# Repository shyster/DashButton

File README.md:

# DashButton
Dash Button ESP8266
Kulasov Vladislav
kulasov[@]gmail.com

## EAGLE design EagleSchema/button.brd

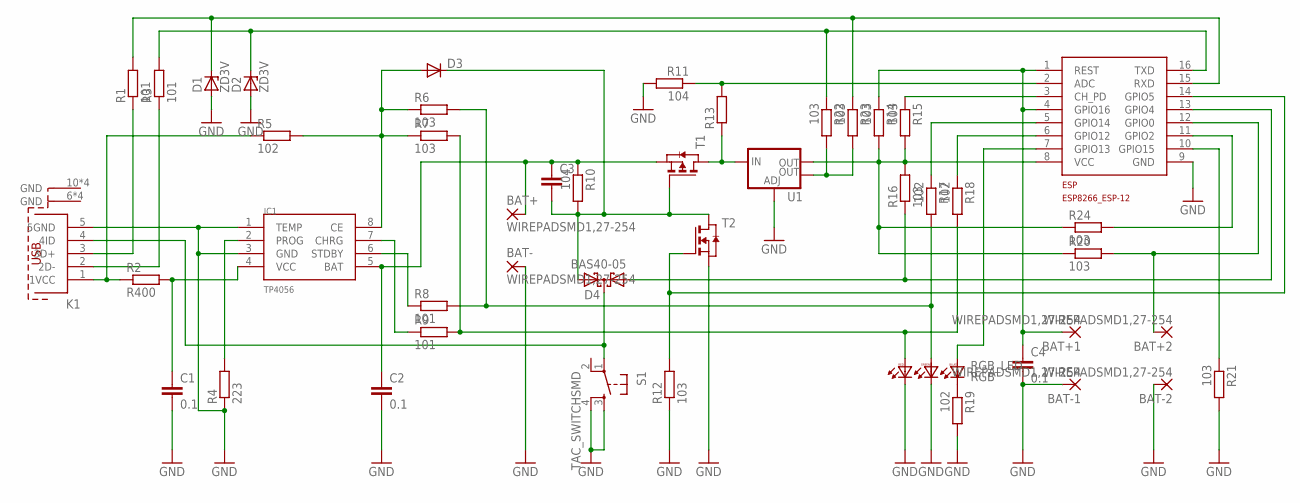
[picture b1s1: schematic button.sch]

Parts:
BAT+, BAT+1, BAT+2: WIREPADSMD1,27-254; SMD1,27-2,54
BAT-, BAT-1, BAT-2: WIREPADSMD1,27-254; SMD1,27-2,54
C1, C2, C4: 0.1; C1206K
C3: C-EUC1206K; C1206K
D1, D2: ZD3V; SOD123
D3: DIODE-SOD123; SOD123
D4: BAS40-05; SOT23
ESP: ESP8266_ESP-12GPIO04/05_CORRECTED; ESP8266-ESP12
IC1: TP4056; SOP-8
K1: 629105150921
R1, R3, R8, R9: 101; R0603
R2: R400; R1206
R4: 223; R0603
R5, R17, R18, R19: 102; R0603
R6, R7, R12, R14, R15, R16, R20, R21, R22, R23, R24: 103; R0603
R10, R11: 104; R0603
R13: R-EU_R0603; R0603
RGB_LED: RGB
S1: TAC_SWITCHSMD; TACTILE-SWITCH-SMD
T1: PMOSSOT23; SOT-23
T2: NMOSSOT23; SOT-23
U1: V_REG_LM1117SOT223; SOT223

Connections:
GND: BAT-.1, BAT-1.1, BAT-2.1, C1.2, C2.2, C4.2, D1.A, D2.A, ESP.9 (GND), IC1.1 (TEMP), IC1.3 (GND), K1.5 (5GND), R4.1, R11.2, R12.1, R19.2, R21.2, RGB_LED.5 (RC), RGB_LED.6 (GC), S1.3, S1.4, T2.2 (S), U1.1 (ADJ)
unnamed: R13.1, T1.1 (D), U1.3 (IN)
unnamed: C3.2, D3.C, D4.2 (A2), R10.2, T1.3 (G), T2.1 (D)
unnamed: D4.1 (A1), ESP.13 (GPIO4), R16.1
unnamed: BAT+.1, C2.1, C3.1, IC1.5 (BAT), R10.1, T1.2 (S)
unnamed: ESP.14 (GPIO5), R12.2, T2.3 (G)
unnamed: ESP.3 (CH_PD), R15.1
unnamed: BAT+1.1, C4.1, ESP.1 (REST), ESP.4 (GPIO16), R14.1
unnamed: ESP.7 (GPIO13), RGB_LED.3 (BA)
unnamed: R19.1, RGB_LED.4 (BC)
unnamed: BAT+2.1, ESP.12 (GPIO0), R20.2
unnamed: ESP.10 (GPIO15), R21.1
unnamed: ESP.8 (VCC), R14.2, R15.2, R16.2, R20.1, R24.1, U1.2 (OUT)
unnamed: D4.3 (C), K1.4 (4ID), S1.1
unnamed: ESP.6 (GPIO12), R18.1
unnamed: ESP.2 (ADC), R11.1, R13.2
unnamed: ESP.11 (GPIO2), R24.2
unnamed: ESP.5 (GPIO14), R17.1
unnamed: IC1.6 (STDBY), R8.1
unnamed: IC1.2 (PROG), R4.2
unnamed: C1.1, IC1.4 (VCC), R2.2
unnamed: K1.1 (1VCC), R2.1, R5.1
unnamed: IC1.7 (CHRG), R9.1
unnamed: K1.3 (3D+), R1.1
unnamed: K1.2 (2D-), R3.1
unnamed: D1.C, ESP.15 (RXD), R1.2, R23.1
unnamed: D2.C, ESP.16 (TXD), R3.2, R22.1
unnamed: R22.2, R23.2, U1.4 (OUT)
unnamed: R7.2, R9.2, R18.2, RGB_LED.2 (RA)
unnamed: R6.2, R8.2, R17.2, RGB_LED.1 (GA)
unnamed: D3.A, IC1.8 (CE), R5.2, R6.1, R7.1

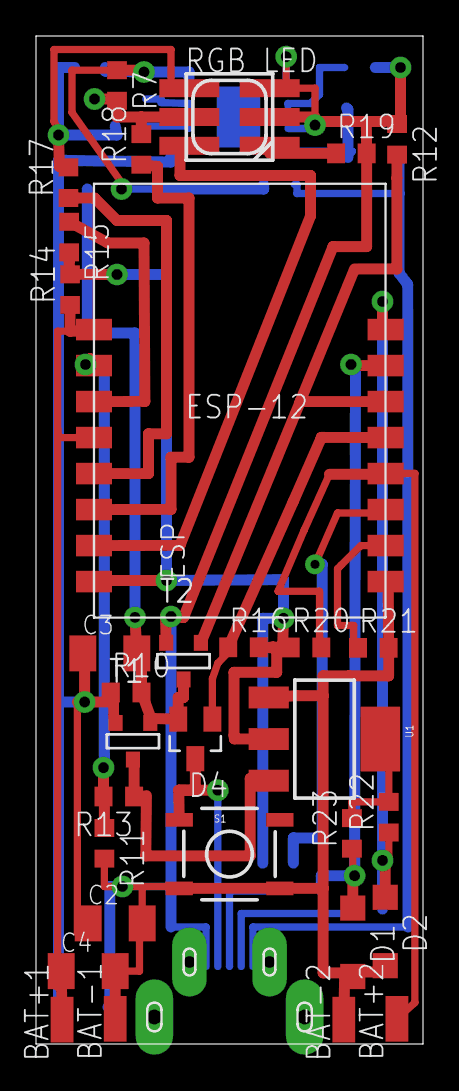
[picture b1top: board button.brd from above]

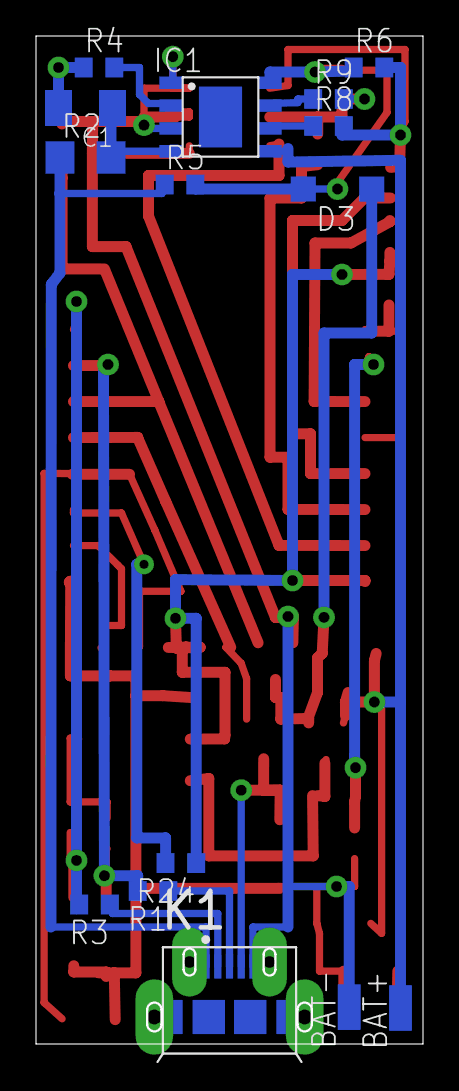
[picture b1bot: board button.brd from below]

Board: 2 copper layers, 21.5 x 56.0 mm, 46 parts (15 on the bottom side), 31 nets.

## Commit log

2017-05-22 new version

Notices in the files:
parts and their libraries:
SparkFun-Retired: Licensing:Creative Commons ShareAlike 4.0 International - https://creativecommons.org/licenses/by-sa/4.0
Input-Output_Connectors_rev15d: Copyright: Würth Elektronik
